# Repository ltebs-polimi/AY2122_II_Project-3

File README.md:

# Electronic Technologies and Biosensors Lab - Project 3
# Academic Year 2021/2022 - II Semester

## Smart tennis racket able to monitor and classify technical tennis movements

**GOAL**

Classification of the three main tennis shots (forehand, backhand and serve) using a tennis racket equipped with an IMU sensor.

**PROJECT SPECIFICATIONS** 

To pursue this goal we had to: 

*	Acquire and process raw accelerometer and gyroscope data from an IMU sensor.
*   Use a Bluetooth module for real-time communication between the microcontroller and the PC to make the device pluggable on a real racket.
*   Program a classification algorithm for gesture recognition.
*	Provide the end player with a Graphical User Interface to visualize in real-time the type of shots predicted during the match. 
*	Print the custom PCB to reduce instrumentation bulkiness. 
*	Design a 3D printed case that includes the microcontroller and the whole instrumentation. 

**CLINICAL NEEDS**

This project addresses the following clinical needs: 

* Sport performance &#x2192; Recognizing and taking memory of shots is a feature that could simplify the work of tennis trainers, that still take notes manually, to understand if the athletes are developing some fundamentals at expenses of the others. 
In the future, associating the information about the type of shot with the corresponding number of points scored by the player can be useful to understand which are the strengths and the weaknesses of the player and therefore to better target the training. 

* Prevention &#x2192; Epicondylitis is an inflammation of the wrist extensor muscles, at their point of insertion.
It is a consequence of repeated microtraumas over time, typical of those who play tennis.
Some experts state that from 10% to 50% of cases this pathology is due to an incorrect technique of execution of the backhand. 
Therefore, the number of backhand shots made by the tennis player could be a useful information for this purpose.

**HARDWARE** 

On the custom PCB are plugged the following components: 

* PSoC microcontroller &#x2192; 3.3V - 5V of power supply
* 9V battery
* Voltage regulator LM7805 (9V to 5V)
* MPU9250 9-axis IMU sensor &#x2192; 5V of power supply
* Bluetooth module HC-06 &#x2192; 3.3V - 5V power supply 

**DEVICE DESIGN** 

Two 3D printed components, fixed together: 

* Housing of the PCB to be interlocked to the handle of the tennis racket.
* Cap of the case.

**PROBLEMS ENCOUNTERED** 

* The FIFO buffer was not used: the datasheet of the MPU9250 was cryptic, and the implementation very difficult and time consuming. So, we decided to read the data from the IMU continuously by using an interrupt. 

* We could not use the switch button: the problem was in the interrupt used to read the data, that did not allow the button to change its state. We partially fixed this problem by adding a button on the GUI. 

* We could not use the LED on the PCB: the problem was with the PCB trace that linked the LED with the ground plane. We partially solved this problem by adding a LED on the GUI. 

**FUTURE DEVELOPMENTS**

The system we have obtained up to now can be further improved by:
* Combining the intertial measurements with dynamic force sensor measurements (FSR), so as to fully characterize the tennis stroke.
* Calculate meaningful parameters from accelerations through more in-depth data post-processing, useful for biomechanical analysis.
* Visualization of the obtained data plots on the GUI.

-----------------

**Organization of the Github repository**

* *3DPrinting_PCB* &#x2192; design of the 3D prints with Fusion 360
* *Acquisitions* &#x2192; CSV files and Python code to train the classifier
* *Biblio* &#x2192; literature
* *Datasheets* &#x2192; HW components' datasheets
* *PCB* &#x2192; design of the custom PCB with Eagle
* *PSOC_firmware* &#x2192; C code to program PSOC microcontroller and HW components 
* *Python_serial* &#x2192; Python code to acquire, decode, classify and display data on the implemented GUI

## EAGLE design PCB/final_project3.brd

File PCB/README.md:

## Electronic Technologies and Biosensors Lab - Project 3
## Academic Year 2021/2022 - II Semester

# PCB DESIGN with EAGLE 

To develop the PCB with EAGLE, instead of using the symbols and footprints of the various components, we used the Connectors from the *Sparkfun* library.
In this way we used all the available space and we developed a more compact PCB.

We used:
- For the PSOC &#x2192; 22 connectors, carefully spaced in order to follow the component dimensions.
- For the IMU &#x2192; 6 connectors, carefully spaced in order to follow the component dimensions.
- For the HC-06 Bluetooth module &#x2192; 4 connectors in order to follow the component dimensions.
- For the voltage regulator &#x2192; 3 connectors.
- For the battery &#x2192; 2 connectors.
- For the LED and for the button (not used later on) &#x2192; 2 connectors. 
- For the 330&#8486; LED resistance (not used later on) &#x2192; component symbol and footprint.  

After developing the PCB with the standard procedure we soldered the female headers on it and we added the components.

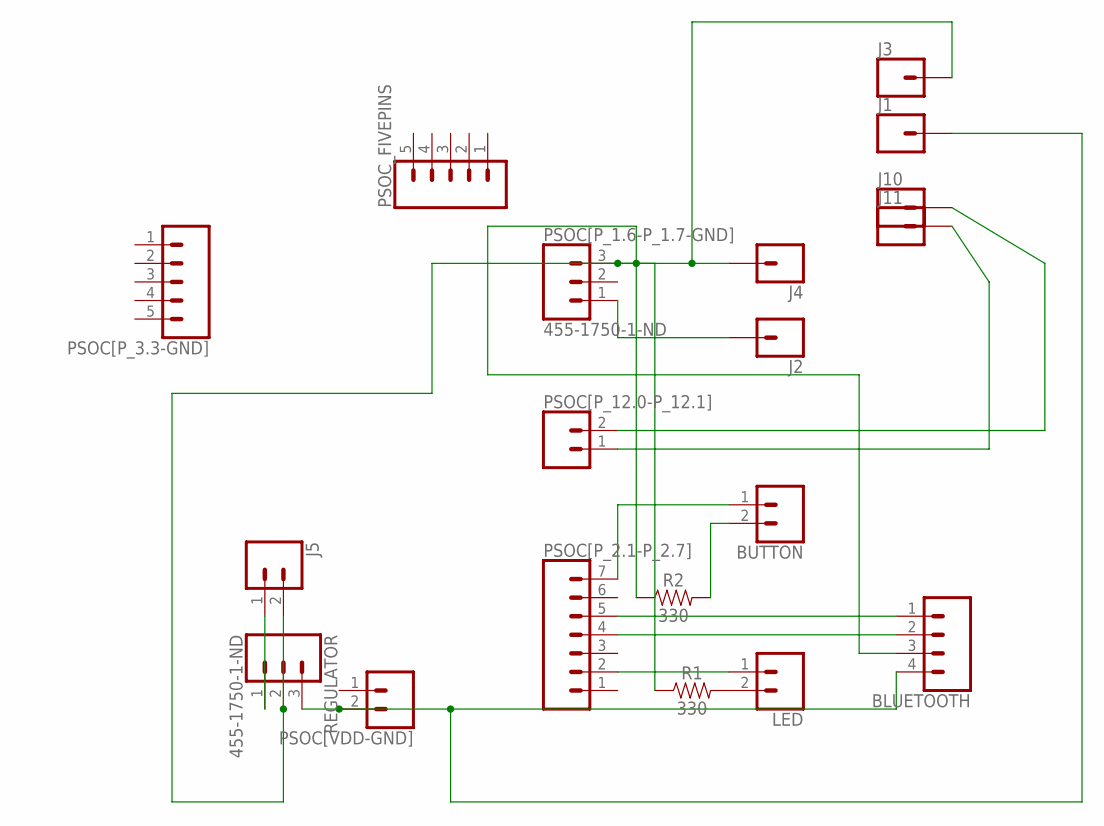
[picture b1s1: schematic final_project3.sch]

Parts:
BLUETOOTH: CONN_04; 1X04
BUTTON: CONN_02; 1X02
J1, J2, J3, J4, J10, J11: CONN_01; 1X01
J5: CONN_02; 1X02
LED: CONN_02; 1X02
PSOC[P_1.6-P_1.7-GND]: 455-1750-1-ND; 1X03
PSOC[P_2.1-P_2.7]: CONN_07; 1X07
PSOC[P_3.3-GND]: CONN_05; 1X05
PSOC[P_12.0-P_12.1]: CONN_02; 1X02
PSOC[VDD-GND]: CONN_02; 1X02
PSOC_FIVEPINS: CONN_05; 1X05
R1, R2: 330; AXIAL-0.3
REGULATOR: 455-1750-1-ND; 1X03

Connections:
BUTTON: BUTTON.1, PSOC[P_2.1-P_2.7].7
GND3: BLUETOOTH.3, J3.1, J4.1, J5.2, PSOC[P_1.6-P_1.7-GND].3, R1.P$1 (1), R2.P$1 (1), REGULATOR.2
LED: LED.1, PSOC[P_2.1-P_2.7].2
unnamed: J5.1, REGULATOR.1
unnamed: J2.1, PSOC[P_1.6-P_1.7-GND].1
unnamed: J11.1, PSOC[P_12.0-P_12.1].1
unnamed: J10.1, PSOC[P_12.0-P_12.1].2
RX_BT-TX_PSOC: BLUETOOTH.1, PSOC[P_2.1-P_2.7].5
R_BUTTON: BUTTON.2, R2.P$2 (2)
R_LED: LED.2, R1.P$2 (2)
TX_BT-RX_PSOC: BLUETOOTH.2, PSOC[P_2.1-P_2.7].4
VDD: BLUETOOTH.4, J1.1, PSOC[VDD-GND].2, REGULATOR.3

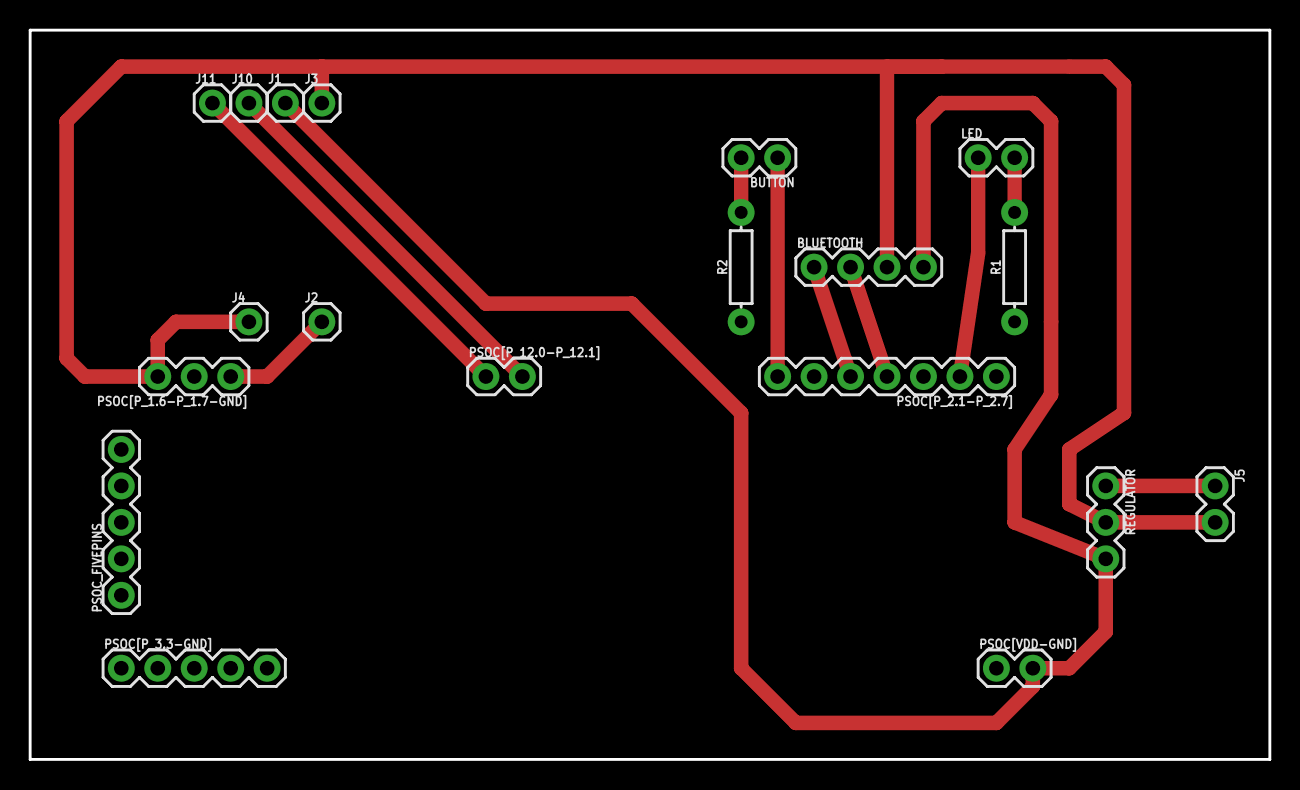
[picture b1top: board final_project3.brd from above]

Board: 2 copper layers, 86.4 x 50.8 mm, 19 parts (0 on the bottom side), 12 nets.

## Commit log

2022-05-09 Added base .gitignore
2022-05-09 Docs folder renamed as Biblio
2022-05-20 Addind schematic
2022-05-20 Adding schematic
2022-05-20 Schematic modification, board
2022-05-24 Correction
2022-05-25 Firmware updated
2022-05-25 specifiche di progetto - prima bozza
2022-05-25 Created folder for 3D printer files
2022-05-25 Uploaded components' datasheets
2022-05-25 AddCADpcb
2022-05-25 Final
2022-06-08 serial reading of N packets of data
2022-06-08 Updated firmware code - removing FIFO
2022-06-10 removing old files
2022-06-10 added folder for GUI
2022-06-10 moved gui file into new folder
2022-06-15 Changed pin BT according to PCB
2022-06-21 Updated n_frames within a packet
2022-06-21 Updated n_frames within a packet and BT settings
2022-06-23 first acquisitions data & training of the classifier
2022-06-24 Trained random forest on acquisitions of 23.06
2022-06-27 GUI in Python and Jupyter Notebook versions
2022-06-29 Updated structure of firmware PSoC code
2022-06-29 Deleted old PSoC firmware code
2022-06-29 Training of different classifiers on data of 23.06 and 29.06
2022-06-29 Upload of 29.06 new acquisitions' data
2022-06-29 Random forest to classify data collected via BT
2022-06-29 Removed old ipynb files
2022-07-01 Upload README file for PCB EAGLE design
2022-07-01 Upload README file for PSoC code and refined Top Design
2022-07-01 Upload acquisitions files and ipynb code for training classifiers
2022-07-01 Upload final training dataset with 56000 rows
2022-07-01 Upload README file for data collection and predictions python code
2022-07-01 Changed location to some folders
2022-07-04 Upload acquisition protocol file
2022-07-04 Upload README Fusion360
2022-07-04 Upload GUI.py in Python_serial folder
2022-07-04 Update PSOC firmware
2022-07-04 Upload README for Github repository
2022-07-04 Rename README_python.md to README.md
2022-07-04 Rename README_PSoC.md to README.md
2022-07-04 Rename README_PCB.md to README.md
2022-07-04 Upload new training dataset with new explanatory variables
2022-07-04 Upload new classification algorithm
2022-07-04 modified acquisition protocol
2022-07-04 Updated new classification algorithm
2022-07-05 Uplaod training set with new acquisitions
2022-07-06 Upload final PSOC firmware
2022-07-06 .py code for data collection and GUI
2022-07-06 Upload new acquisition files
2022-07-06 Upload new training dataset
2022-07-06 Renamed training dataset
2022-07-06 Removed old .py files
2022-07-06 removed project specification file to be replaced with a README
2022-07-06 Modified comments
2022-07-06 Create new README file for python code
2022-07-06 Renamed folders
2022-07-07 Update all the README files
2022-07-07 Final python code
2022-07-08 Upload new README for the Acquisitions folder
2022-07-08 Updated .c and .h files
2022-07-08 Updated ..ipynb file
2022-07-08 Substituted HC-05 with HC-06 BT datasheet
2022-07-08 Updated all README files
2022-07-08 Updated README.md format
2022-07-14 Upload final PPT presentation
2022-07-14 Upload DEMO videoo

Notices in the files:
parts and their libraries:
SparkFun-Connectors: Licensing: Creative Commons ShareAlike 4.0 International - https://creativecommons.org/licenses/by-sa/4.0
